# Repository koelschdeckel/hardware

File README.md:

Introduction
============

^^dkl is an Open Source hardware project that is being developed in
cooperation between the City of Cologne and Press Any Key UG. The
platform is intended to bridge the gap between devices similar to
Arduino, which allow physical access to sensors via electronic protocols
and device like Raspberry Pi that allow comfortable programming and
access to higher level facilities like Ethernet, USB and Bluetooth at
the cost of system complexity.

The system is intended to be used with applications that require
immediate interaction with the physical world, but need to interact with
the Internet or user devices. Furthermore, technical expertise required
to customise and operate the platform should be reduced to a minimum.

[Find out more](http://koelschdeckel.github.io/)

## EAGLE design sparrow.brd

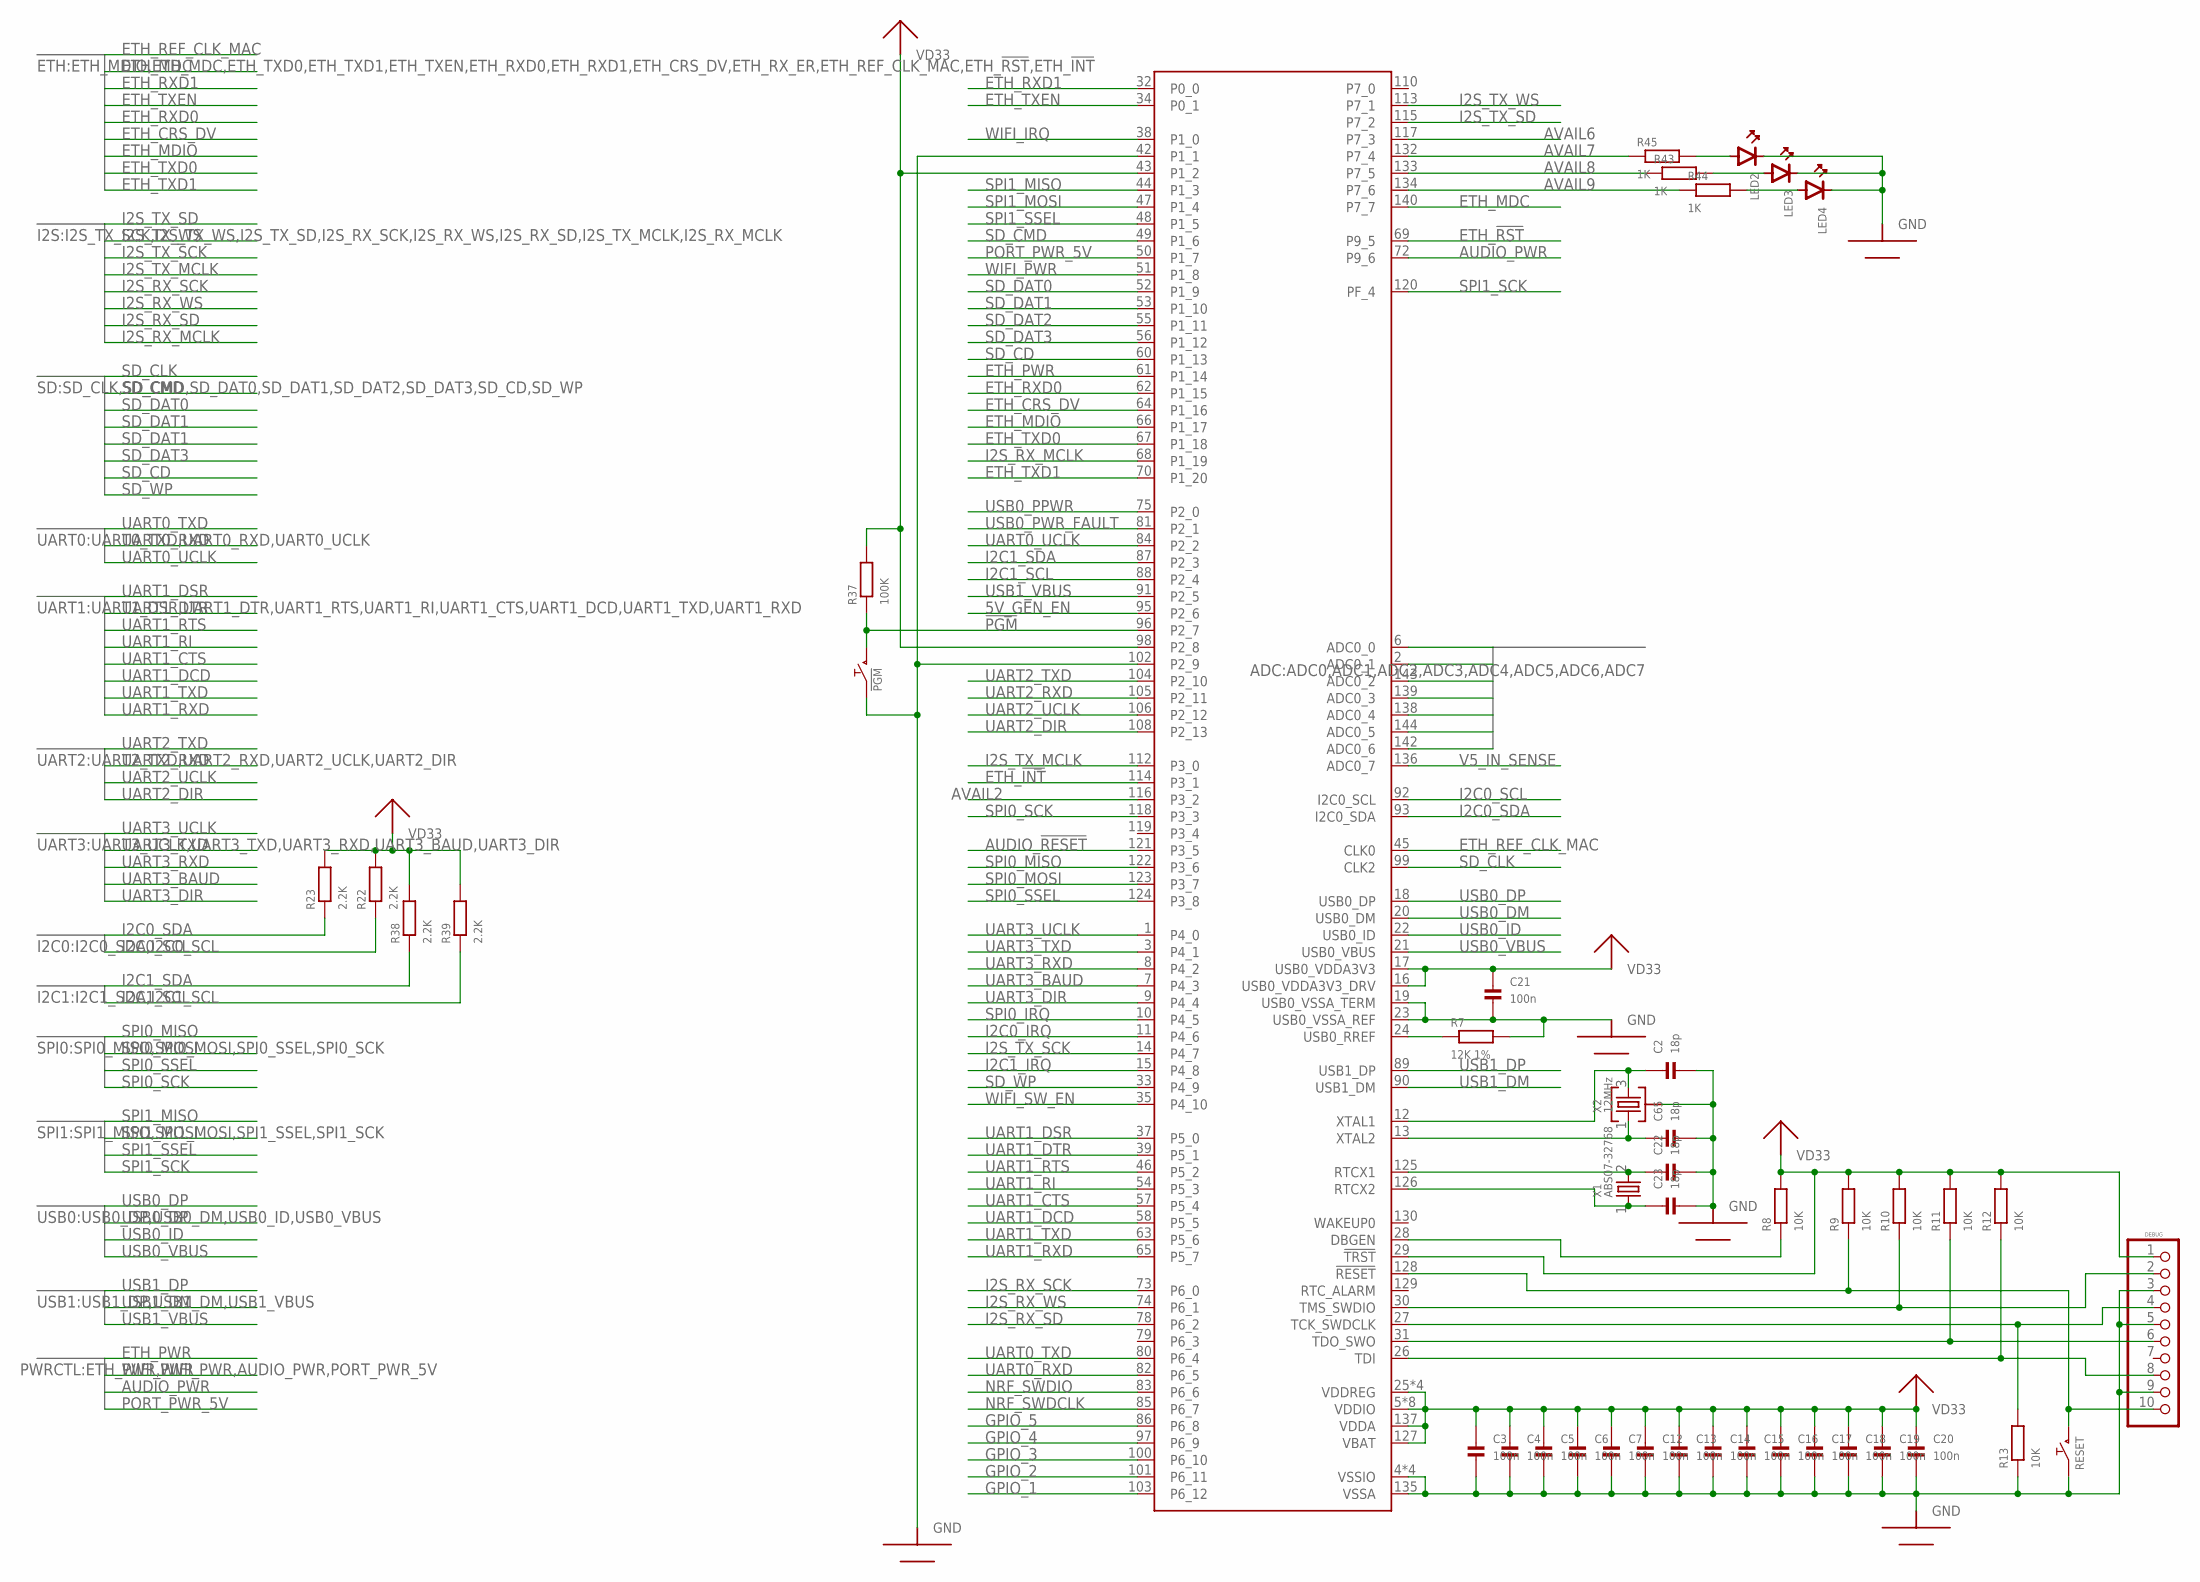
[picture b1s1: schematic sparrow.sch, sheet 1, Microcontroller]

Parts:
!PGM: PUSHBUTTONKMR2XX; CK-KMR2
C2, C22, C23, C65: 18p; 0603
C3, C4, C5, C6, C7, C12, C13, C14, C15, C16, C17, C18, C19, C20, C21: 100n; 0603
LED2, LED3, LED4: LED0603; 0603_POLAR
LPC_DEBUG: DEBUG; 2X05_SMT
MCU: LPC1837; QFP144-0.5
R7: 12K 1%; 0603
R8, R9, R10, R11, R12, R13: 10K; 0603
R22, R23, R38, R39: 2.2K; 0603
R37: 100K; 0603
R43, R44, R45: 1K; 0603
RESET: PUSHBUTTONKMR2XX; CK-KMR2
X1: ABS07-32768; 1206_MINIMELF_COMBO
X2: 12MHz; ABM8G

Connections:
5V_GEN_EN: MCU.95 (P2_6); also elsewhere on the board
!PGM: !PGM.P$3 (2), !PGM.P$4 (2), MCU.96 (P2_7), R37.1
!RESET: LPC_DEBUG.10, MCU.128 (!RESET), R9.1, RESET.P$3 (2), RESET.P$4 (2)
ADC0: MCU.6 (ADC0_0); also elsewhere on the board
ADC1: MCU.2 (ADC0_1); also elsewhere on the board
ADC2: MCU.143 (ADC0_2); also elsewhere on the board
ADC3: MCU.139 (ADC0_3); also elsewhere on the board
ADC4: MCU.138 (ADC0_4); also elsewhere on the board
ADC5: MCU.144 (ADC0_5); also elsewhere on the board
ADC6: MCU.142 (ADC0_6); also elsewhere on the board
AUDIO_!RESET: MCU.121 (P3_5); also elsewhere on the board
AUDIO_PWR: MCU.72 (P9_6); also elsewhere on the board
AVAIL2: MCU.116 (P3_2)
AVAIL6: MCU.117 (P7_3)
AVAIL7: MCU.132 (P7_4), R45.1
AVAIL8: MCU.133 (P7_5), R43.1
AVAIL9: MCU.134 (P7_6), R44.1
DBGEN: MCU.28 (DBGEN), R8.1
ETH_!INT: MCU.114 (P3_1); also elsewhere on the board
ETH_!RST: MCU.69 (P9_5); also elsewhere on the board
ETH_CRS_DV: MCU.64 (P1_16); also elsewhere on the board
ETH_MDC: MCU.140 (P7_7); also elsewhere on the board
ETH_MDIO: MCU.66 (P1_17); also elsewhere on the board
ETH_PWR: MCU.61 (P1_14); also elsewhere on the board
ETH_REF_CLK_MAC: MCU.45 (CLK0); also elsewhere on the board
ETH_RXD0: MCU.62 (P1_15); also elsewhere on the board
ETH_RXD1: MCU.32 (P0_0); also elsewhere on the board
ETH_TXD0: MCU.67 (P1_18); also elsewhere on the board
ETH_TXD1: MCU.70 (P1_20); also elsewhere on the board
ETH_TXEN: MCU.34 (P0_1); also elsewhere on the board
GND: !PGM.P$1 (1), !PGM.P$2 (1), C2.2, C3.2, C4.2, C5.2, C6.2, C7.2, C12.2, C13.2, C14.2, C15.2, C16.2, C17.2, C18.2, C19.2, C20.2, C21.2, C22.2, C23.2, C65.2, LED2.K (CATHODE), LED3.K (CATHODE), LED4.K (CATHODE), LPC_DEBUG.3, LPC_DEBUG.5, LPC_DEBUG.9, MCU.4 (VSSIO), MCU.19 (USB0_VSSA_TERM), MCU.23 (USB0_VSSA_REF), MCU.40 (VSSIO), MCU.42 (P1_1), MCU.76 (VSSIO), MCU.102 (P2_9), MCU.109 (VSSIO), MCU.135 (VSSA), R7.2, R13.1, RESET.P$1 (1), RESET.P$2 (1), X2.2 (GND), X2.4 (GND); also elsewhere on the board
GPIO_1: MCU.103 (P6_12); also elsewhere on the board
GPIO_2: MCU.101 (P6_11); also elsewhere on the board
GPIO_3: MCU.100 (P6_10); also elsewhere on the board
GPIO_4: MCU.97 (P6_9); also elsewhere on the board
GPIO_5: MCU.86 (P6_8); also elsewhere on the board
I2C0_IRQ: MCU.11 (P4_6); also elsewhere on the board
I2C0_SCL: MCU.92 (I2C0_SCL), R22.1; also elsewhere on the board
I2C0_SDA: MCU.93 (I2C0_SDA), R23.1; also elsewhere on the board
I2C1_IRQ: MCU.15 (P4_8); also elsewhere on the board
I2C1_SCL: MCU.88 (P2_4), R39.1; also elsewhere on the board
I2C1_SDA: MCU.87 (P2_3), R38.1; also elsewhere on the board
I2S_RX_MCLK: MCU.68 (P1_19); also elsewhere on the board
I2S_RX_SCK: MCU.73 (P6_0); also elsewhere on the board
I2S_RX_SD: MCU.78 (P6_2); also elsewhere on the board
I2S_RX_WS: MCU.74 (P6_1); also elsewhere on the board
I2S_TX_MCLK: MCU.112 (P3_0); also elsewhere on the board
I2S_TX_SCK: MCU.14 (P4_7); also elsewhere on the board
I2S_TX_SD: MCU.115 (P7_2); also elsewhere on the board
I2S_TX_WS: MCU.113 (P7_1); also elsewhere on the board
unnamed: LED2.A (ANODE), R45.2
unnamed: LED3.A (ANODE), R43.2
unnamed: LED4.A (ANODE), R44.2
NRF_SWDCLK: MCU.85 (P6_7); also elsewhere on the board
NRF_SWDIO: MCU.83 (P6_6); also elsewhere on the board
PORT_PWR_5V: MCU.50 (P1_7); also elsewhere on the board
RTXC1: C22.1, MCU.125 (RTCX1), X1.2
RTXC2: C23.1, MCU.126 (RTCX2), X1.1
SD_CD: MCU.60 (P1_13); also elsewhere on the board
SD_CLK: MCU.99 (CLK2); also elsewhere on the board
SD_CMD: MCU.49 (P1_6); also elsewhere on the board
SD_DAT0: MCU.52 (P1_9); also elsewhere on the board
SD_DAT1: MCU.53 (P1_10); also elsewhere on the board
SD_DAT2: MCU.55 (P1_11); also elsewhere on the board
SD_DAT3: MCU.56 (P1_12); also elsewhere on the board
SD_WP: MCU.33 (P4_9); also elsewhere on the board
SPI0_IRQ: MCU.10 (P4_5); also elsewhere on the board
SPI0_MISO: MCU.122 (P3_6); also elsewhere on the board
SPI0_MOSI: MCU.123 (P3_7); also elsewhere on the board
SPI0_SCK: MCU.118 (P3_3); also elsewhere on the board
SPI0_SSEL: MCU.124 (P3_8); also elsewhere on the board
SPI1_MISO: MCU.44 (P1_3); also elsewhere on the board
SPI1_MOSI: MCU.47 (P1_4); also elsewhere on the board
SPI1_SCK: MCU.120 (PF_4); also elsewhere on the board
SPI1_SSEL: MCU.48 (P1_5); also elsewhere on the board
SWDCLK: LPC_DEBUG.4, MCU.27 (TCK_SWDCLK), R13.2
SWDIO: LPC_DEBUG.2, MCU.30 (TMS_SWDIO), R10.1
TDI: LPC_DEBUG.8, MCU.26 (TDI), R12.1
TDO_SWO: LPC_DEBUG.6, MCU.31 (TDO_SWO), R11.1
UART0_RXD: MCU.82 (P6_5); also elsewhere on the board
UART0_TXD: MCU.80 (P6_4); also elsewhere on the board
UART0_UCLK: MCU.84 (P2_2); also elsewhere on the board
UART1_CTS: MCU.57 (P5_4); also elsewhere on the board
UART1_DCD: MCU.58 (P5_5)
UART1_DSR: MCU.37 (P5_0)
UART1_DTR: MCU.39 (P5_1)
UART1_RI: MCU.54 (P5_3)
UART1_RTS: MCU.46 (P5_2); also elsewhere on the board
UART1_RXD: MCU.65 (P5_7); also elsewhere on the board
UART1_TXD: MCU.63 (P5_6); also elsewhere on the board
UART2_DIR: MCU.108 (P2_13); also elsewhere on the board
UART2_RXD: MCU.105 (P2_11); also elsewhere on the board
UART2_TXD: MCU.104 (P2_10); also elsewhere on the board
UART2_UCLK: MCU.106 (P2_12); also elsewhere on the board
UART3_BAUD: MCU.7 (P4_3); also elsewhere on the board
UART3_DIR: MCU.9 (P4_4); also elsewhere on the board
UART3_RXD: MCU.8 (P4_2); also elsewhere on the board
UART3_TXD: MCU.3 (P4_1); also elsewhere on the board
UART3_UCLK: MCU.1 (P4_0); also elsewhere on the board
USB0_DM: MCU.20 (USB0_DM); also elsewhere on the board
USB0_DP: MCU.18 (USB0_DP); also elsewhere on the board
USB0_ID: MCU.22 (USB0_ID); also elsewhere on the board
USB0_PPWR: MCU.75 (P2_0); also elsewhere on the board
USB0_PWR_FAULT: MCU.81 (P2_1); also elsewhere on the board
USB0_RREF: MCU.24 (USB0_RREF), R7.1
USB0_VBUS: MCU.21 (USB0_VBUS); also elsewhere on the board
USB1_DM: MCU.90 (USB1_DM); also elsewhere on the board
USB1_DP: MCU.89 (USB1_DP); also elsewhere on the board
USB1_VBUS: MCU.91 (P2_5); also elsewhere on the board
V5_IN_SENSE: MCU.136 (ADC0_7); also elsewhere on the board
VD33: C3.1, C4.1, C5.1, C6.1, C7.1, C12.1, C13.1, C14.1, C15.1, C16.1, C17.1, C18.1, C19.1, C20.1, C21.1, LPC_DEBUG.1, MCU.5 (VDDIO), MCU.16 (USB0_VDDA3V3_DRV), MCU.17 (USB0_VDDA3V3), MCU.25 (VDDREG), MCU.29 (!TRST), MCU.36 (VDDIO), MCU.41 (VDDIO), MCU.43 (P1_2), MCU.59 (VDDREG), MCU.71 (VDDIO), MCU.77 (VDDIO), MCU.94 (VDDREG), MCU.98 (P2_8), MCU.107 (VDDIO), MCU.111 (VDDIO), MCU.127 (VBAT), MCU.131 (VDDREG), MCU.137 (VDDA), MCU.141 (VDDIO), R8.2, R9.2, R10.2, R11.2, R12.2, R22.2, R23.2, R37.2, R38.2, R39.2; also elsewhere on the board
WIFI_IRQ: MCU.38 (P1_0); also elsewhere on the board
WIFI_PWR: MCU.51 (P1_8); also elsewhere on the board
WIFI_SW_EN: MCU.35 (P4_10); also elsewhere on the board
XTAL1: C2.1, MCU.12 (XTAL1), X2.3 (2)
XTAL2: C65.1, MCU.13 (XTAL2), X2.1

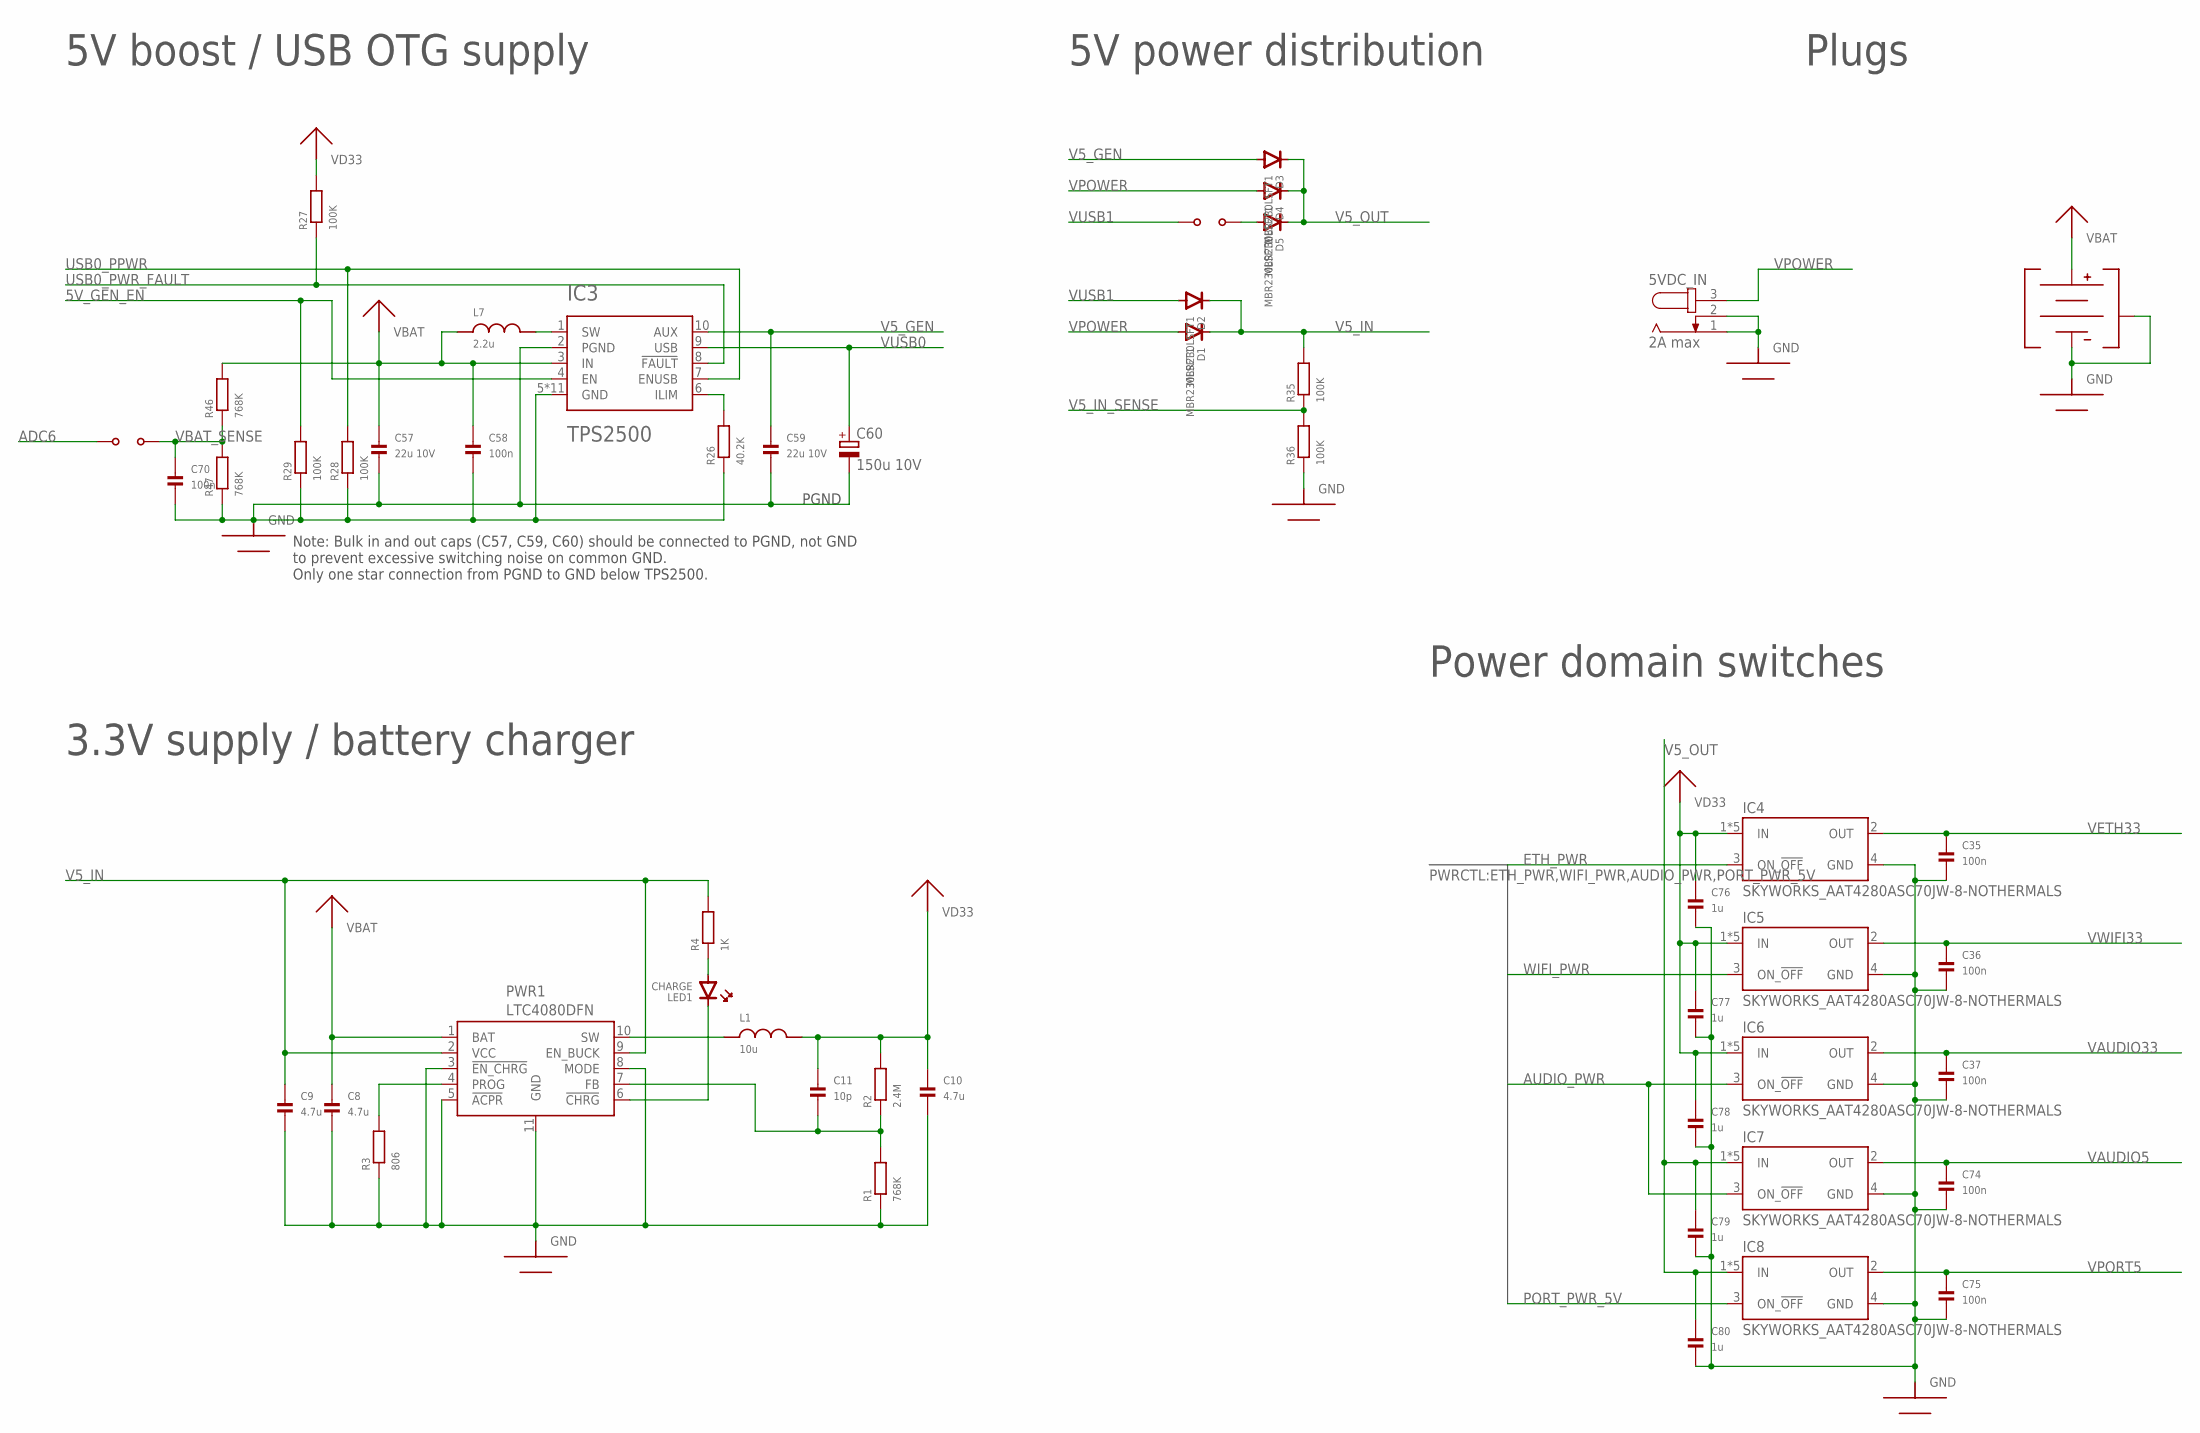
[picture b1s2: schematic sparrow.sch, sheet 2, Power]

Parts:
5VDC_IN: 2A max; CUI_PJ_102BH
BATSNS: JUMPERSOLDER_CLOSED; 0603_SOLDERJUMPER_CLOSED
BATT: BATTERY_WITH_HOLDER; S2B-PH-SM4-TB
C8, C9, C10: 4.7u; 0603
C11: 10p; 0603
C35, C36, C37, C58, C70, C74, C75: 100n; 0603
C57, C59: 22u 10V; 0805
C60: 150u 10V; 1210_POLAR
C76, C77, C78, C79, C80: 1u; 0603
D1, D2, D3, D4, D5: MBR230LSFT1; SOD123FL
IC3: TPS2500; SON10-0.5-EP-VIAS
IC4, IC5, IC6, IC7, IC8: SKYWORKS_AAT4280ASC70JW-8-NOTHERMALS; SC70JW-8-NOTHERMALS
L1: 10u; INDUCTOR_40X40
L7: 2.2u; INDUCTOR_40X40
LED1: CHARGE; 0603_POLAR
LIM: JUMPERSOLDER_OPEN; 0603_SOLDERJUMPER_OPEN
PWR1: LTC4080DFN; LTC4080_DFN
R1, R46, R47: 768K; 0603
R2: 2.4M; 0603
R3: 806; 0603
R4: 1K; 0603
R26: 40.2K; 0603
R27, R28, R29, R35, R36: 100K; 0603

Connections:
5V_BOOST_SW: IC3.1 (SW), L7.P$2 (2)
5V_GEN_EN: IC3.4 (EN), R29.2; also elsewhere on the board
5V_ILIM: IC3.6 (ILIM), R26.2
ADC6: BATSNS.1; also elsewhere on the board
AUDIO_PWR: IC6.3 (ON_!OFF), IC7.3 (ON_!OFF); also elsewhere on the board
CHARGE_!CHRG: LED1.K (CATHODE), PWR1.6 (!CHRG)
CHARGE_!CHRG_CURR: LED1.A (ANODE), R4.1
CHARGE_FB: C11.2, PWR1.7 (FB), R1.2, R2.1
CHARGE_PROG: PWR1.4 (PROG), R3.2
CHARGE_SW: L1.P$1 (1), PWR1.10 (SW)
ETH_PWR: IC4.3 (ON_!OFF); also elsewhere on the board
GND: 5VDC_IN.1, 5VDC_IN.2, BATT.2 (-), BATT.3 (HOLDER), BATT.4 (HOLDER), C8.2, C9.2, C10.2, C35.2, C36.2, C37.2, C57.2, C58.2, C59.2, C60.K (-), C70.2, C74.2, C75.2, C76.2, C77.2, C78.2, C79.2, C80.2, IC3.2 (PGND), IC3.5 (GND), IC3.EXT1 (GND), IC3.EXT2 (GND), IC3.EXT3 (GND), IC3.EXT4 (GND), IC3.PAD (GND), IC3.THERM1 (GND), IC3.THERM2 (GND), IC3.THERM3 (GND), IC3.THERM4 (GND), IC3.THERM5 (GND), IC4.4 (GND), IC5.4 (GND), IC6.4 (GND), IC7.4 (GND), IC8.4 (GND), PWR1.3 (!EN_CHRG), PWR1.5 (!ACPR), PWR1.8 (MODE), PWR1.11 (GND), R1.1, R3.1, R26.1, R28.1, R29.1, R36.1, R47.1; also elsewhere on the board
PORT_PWR_5V: IC8.3 (ON_!OFF); also elsewhere on the board
USB0_PPWR: IC3.7 (ENUSB), R28.2; also elsewhere on the board
USB0_PWR_FAULT: IC3.8 (!FAULT), R27.1; also elsewhere on the board
V5_GEN: C59.1, D3.A (ANODE), IC3.10 (AUX)
V5_IN: C9.1, D1.K (CATHODE), D2.K (CATHODE), PWR1.2 (VCC), PWR1.9 (EN_BUCK), R4.2, R35.2
V5_IN_SENSE: R35.1, R36.2; also elsewhere on the board
V5_OUT: C79.1, C80.1, D3.K (CATHODE), D4.K (CATHODE), D5.K (CATHODE), IC7.1 (IN), IC7.5 (IN), IC7.6 (IN), IC7.7 (IN), IC7.8 (IN), IC8.1 (IN), IC8.5 (IN), IC8.6 (IN), IC8.7 (IN), IC8.8 (IN)
VAUDIO5: C74.1, IC7.2 (OUT); also elsewhere on the board
VAUDIO33: C37.1, IC6.2 (OUT); also elsewhere on the board
VBAT: BATT.1 (+), C8.1, C57.1, C58.1, IC3.3 (IN), L7.P$1 (1), PWR1.1 (BAT), R46.2
VBAT_SENSE: BATSNS.2, C70.1, R46.1, R47.2
VD33: C10.1, C11.1, C76.1, C77.1, C78.1, IC4.1 (IN), IC4.5 (IN), IC4.6 (IN), IC4.7 (IN), IC4.8 (IN), IC5.1 (IN), IC5.5 (IN), IC5.6 (IN), IC5.7 (IN), IC5.8 (IN), IC6.1 (IN), IC6.5 (IN), IC6.6 (IN), IC6.7 (IN), IC6.8 (IN), L1.P$2 (2), R2.2, R27.2; also elsewhere on the board
VETH33: C35.1, IC4.2 (OUT); also elsewhere on the board
VPORT5: C75.1, IC8.2 (OUT); also elsewhere on the board
VPOWER: 5VDC_IN.3, D1.A (ANODE), D4.A (ANODE)
VUSB0: C60.A (+), IC3.9 (USB); also elsewhere on the board
VUSB1: D2.A (ANODE), LIM.1; also elsewhere on the board
VUSB1_V5_OUT: D5.A (ANODE), LIM.2
VWIFI33: C36.1, IC5.2 (OUT); also elsewhere on the board
WIFI_PWR: IC5.3 (ON_!OFF); also elsewhere on the board

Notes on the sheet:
5V power distribution
5V boost / USB OTG supply
3.3V supply / battery charger
Power domain switches
Plugs
Note: Bulk in and out caps (C57, C59, C60) should be connected to PGND, not GND to prevent excessive switching noise on common GND. Only one star connection from PGND to GND below TPS2500.
PGND

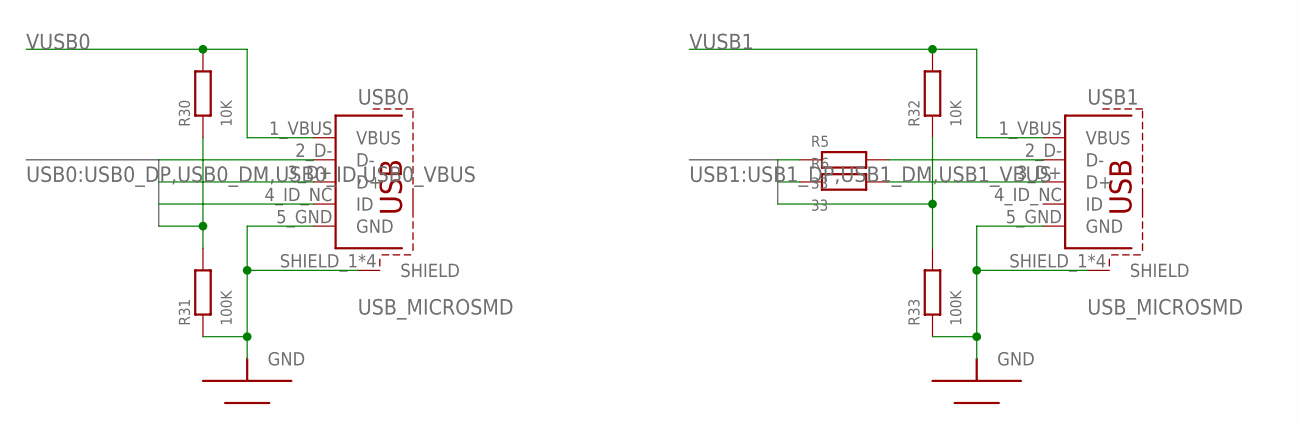
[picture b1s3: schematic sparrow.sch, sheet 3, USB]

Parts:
R5, R6: 33; 0603
R30, R32: 10K; 0603
R31, R33: 100K; 0603
USB0, USB1: USB_MICROSMD; USB_MICRO_SMD

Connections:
GND: R31.1, R33.1, USB0.5_GND (GND), USB0.SHIELD_1 (SHIELD), USB0.SHIELD_2 (SHIELD), USB0.SHIELD_3 (SHIELD), USB0.SHIELD_4 (SHIELD), USB1.5_GND (GND), USB1.SHIELD_1 (SHIELD), USB1.SHIELD_2 (SHIELD), USB1.SHIELD_3 (SHIELD), USB1.SHIELD_4 (SHIELD); also elsewhere on the board
USB0_DM: USB0.2_D- (D-); also elsewhere on the board
USB0_DP: USB0.3_D+ (D+); also elsewhere on the board
USB0_ID: USB0.4_ID_NC (ID); also elsewhere on the board
USB0_VBUS: R30.1, R31.2; also elsewhere on the board
USB1_DM: R5.1; also elsewhere on the board
USB1_DM_LINE: R5.2, USB1.2_D- (D-)
USB1_DP: R6.1; also elsewhere on the board
USB1_VBUS: R32.1, R33.2; also elsewhere on the board
USB_DP_LINE: R6.2, USB1.3_D+ (D+)
VUSB0: R30.2, USB0.1_VBUS (VBUS); also elsewhere on the board
VUSB1: R32.2, USB1.1_VBUS (VBUS); also elsewhere on the board

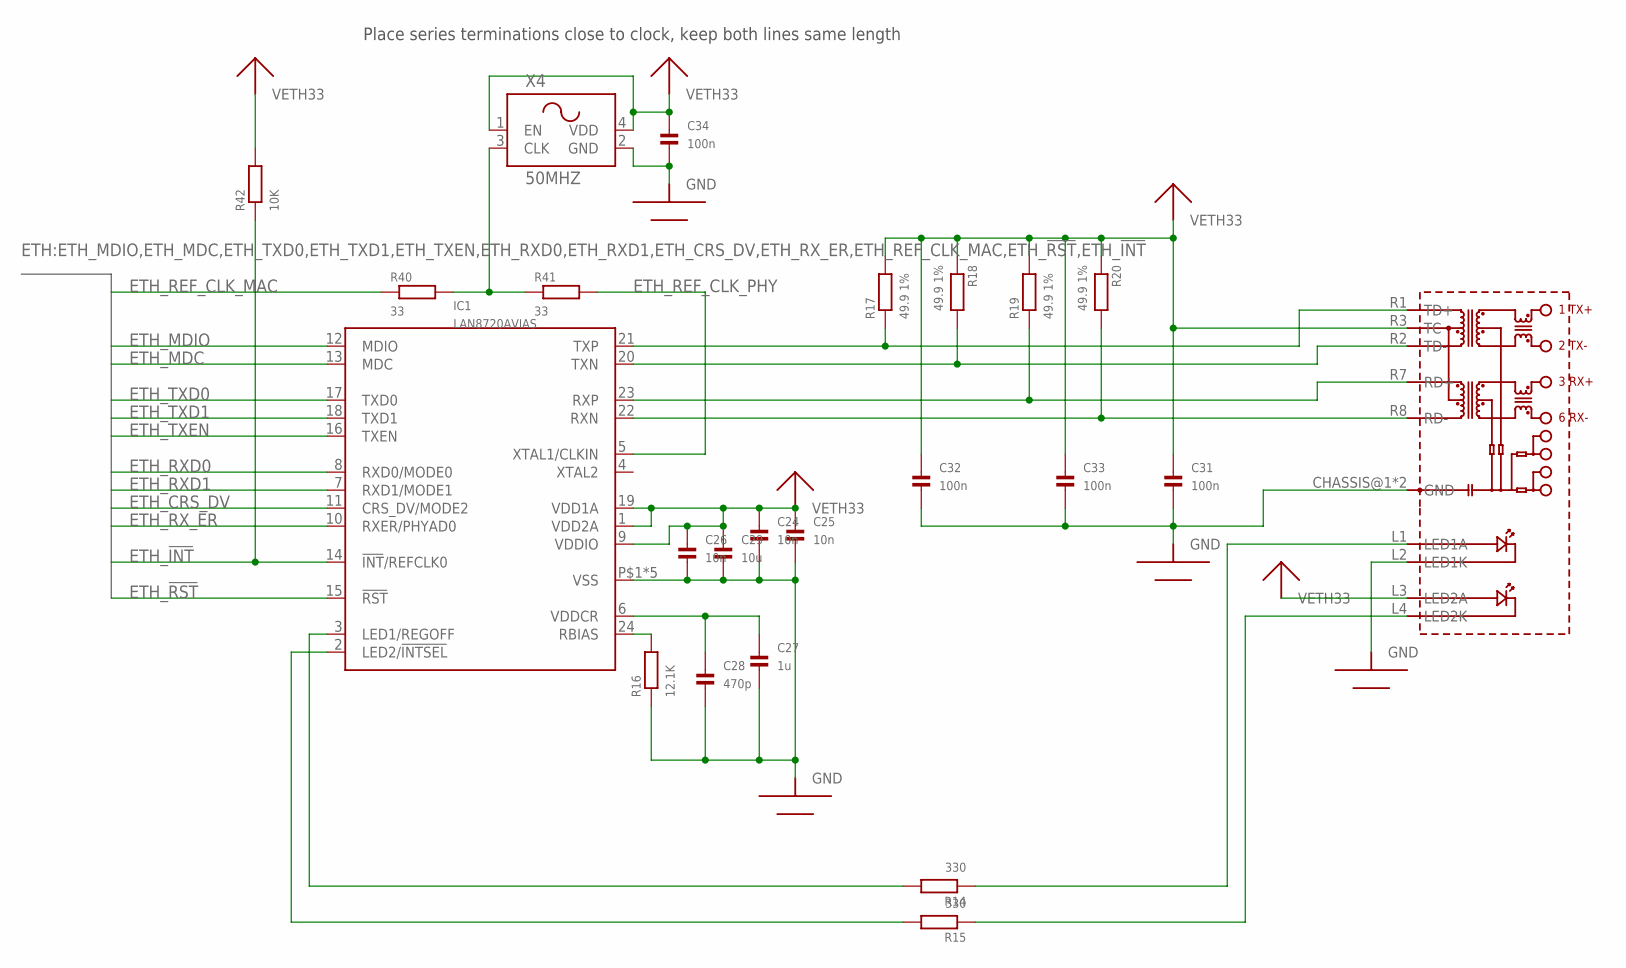
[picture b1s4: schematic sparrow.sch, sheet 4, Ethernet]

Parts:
C24, C25, C26: 10n; 0603
C27: 1u; 0603
C28: 470p; 0603
C29: 10u; 0603
C31, C32, C33, C34: 100n; 0603
ETH: ETHERNET_JACK_LEDSRB1-125BAG1A; RJ45-RB1-125BAG1A
IC1: LAN8720AVIAS; QFN24-0.5-EP-VIAS
R14, R15: 330; 0603
R16: 12.1K; 0603
R17, R18, R19, R20: 49.9 1%; 0603
R40, R41: 33; 0603
R42: 10K; 0603
X4: 50MHZ; CRYSTAL25X20

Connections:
ETH_!INT: IC1.14 (!INT!/REFCLK0), R42.1; also elsewhere on the board
ETH_!RST: IC1.15 (!RST); also elsewhere on the board
ETH_CRS_DV: IC1.11 (CRS_DV/MODE2); also elsewhere on the board
ETH_LED1: IC1.3 (LED1/REGOFF), R14.2
ETH_LED1_CURR: ETH.L1 (LED1A), R14.1
ETH_LED2: IC1.2 (LED2/!INTSEL), R15.2
ETH_LED2_CURR: ETH.L4 (LED2K), R15.1
ETH_MDC: IC1.13 (MDC); also elsewhere on the board
ETH_MDIO: IC1.12 (MDIO); also elsewhere on the board
ETH_RBIAS: IC1.24 (RBIAS), R16.2
ETH_REF_CLK: R40.2, R41.1, X4.3 (CLK)
ETH_REF_CLK_MAC: R40.1; also elsewhere on the board
ETH_REF_CLK_PHY: IC1.5 (XTAL1/CLKIN), R41.2
ETH_RXD0: IC1.8 (RXD0/MODE0); also elsewhere on the board
ETH_RXD1: IC1.7 (RXD1/MODE1); also elsewhere on the board
ETH_RXN: ETH.R8 (RD-), IC1.22 (RXN), R20.2
ETH_RXP: ETH.R7 (RD+), IC1.23 (RXP), R19.1
ETH_RX_ER: IC1.10 (RXER/PHYAD0)
ETH_TXD0: IC1.17 (TXD0); also elsewhere on the board
ETH_TXD1: IC1.18 (TXD1); also elsewhere on the board
ETH_TXEN: IC1.16 (TXEN); also elsewhere on the board
ETH_TXN: ETH.R2 (TD-), IC1.20 (TXN), R18.2
ETH_TXP: ETH.R1 (TD+), IC1.21 (TXP), R17.1
ETH_VDDCR: C27.1, C28.1, IC1.6 (VDDCR)
GND: C24.2, C25.2, C26.2, C27.2, C28.2, C29.2, C31.2, C32.2, C33.2, C34.2, ETH.CHASSIS@1 (GND), ETH.CHASSIS@2 (GND), ETH.L2 (LED1K), IC1.P$1 (VSS), IC1.P$2 (VSS), IC1.P$3 (VSS), IC1.P$4 (VSS), IC1.PAD (VSS), R16.1, X4.2 (GND); also elsewhere on the board
VETH33: C24.1, C25.1, C26.1, C29.1, C31.1, C32.1, C33.1, C34.1, ETH.L3 (LED2A), ETH.R3 (TC), IC1.1 (VDD2A), IC1.9 (VDDIO), IC1.19 (VDD1A), R17.2, R18.1, R19.2, R20.1, R42.2, X4.1 (EN), X4.4 (VDD); also elsewhere on the board

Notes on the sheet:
Place series terminations close to clock, keep both lines same length

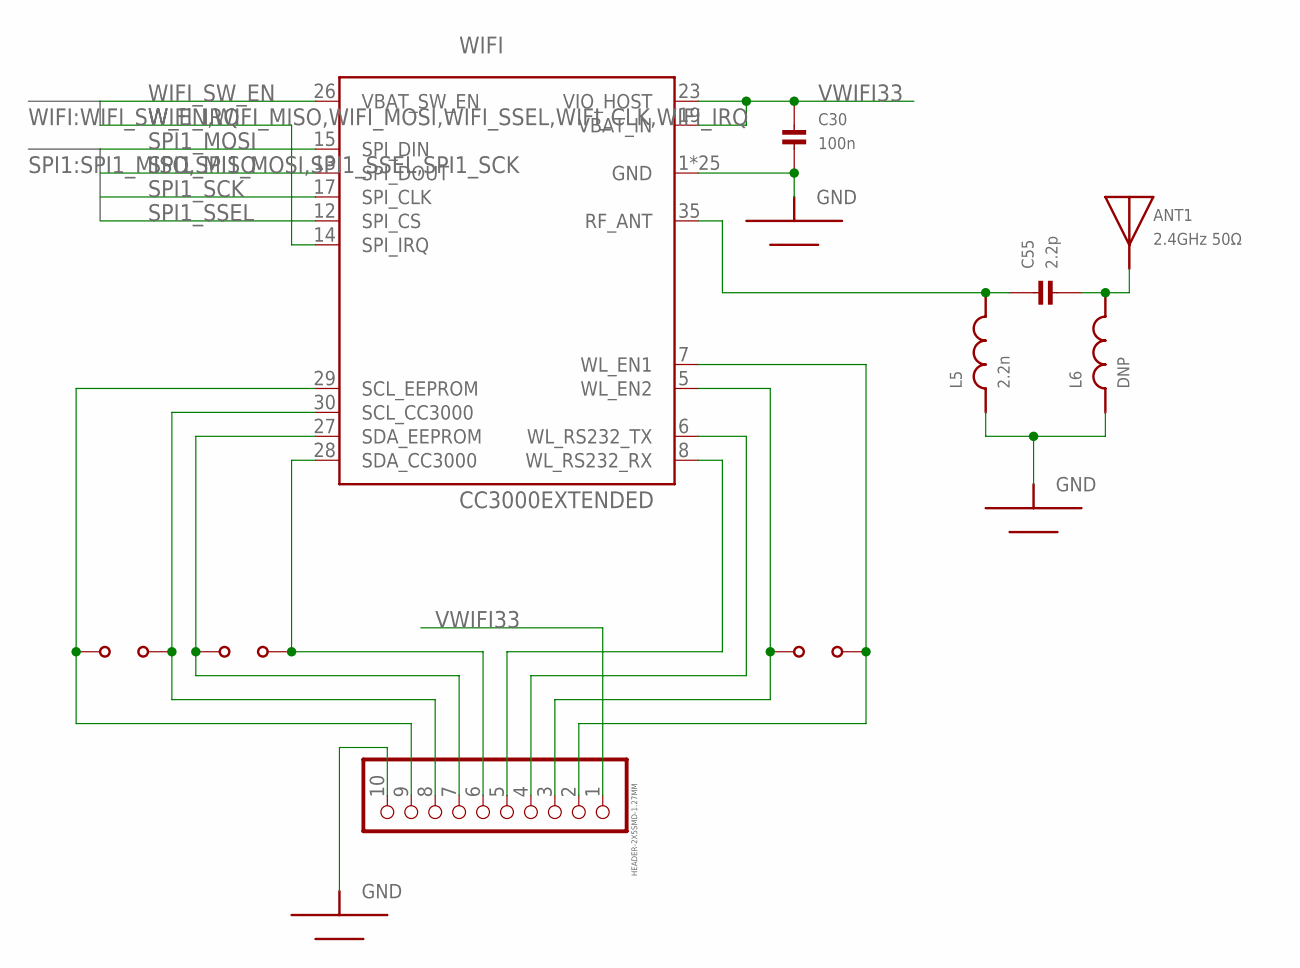
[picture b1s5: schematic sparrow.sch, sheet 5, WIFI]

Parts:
ANT1: 2.4GHz 50Ω; 1206_MINIMELF_COMBO
C30: 100n; 0603
C55: 2.2p; 0402
CC_DEBUG: HEADER-2X5SMD-1.27MM; 2X05_SMT
L5: 2.2n; 0402
L6: DNP; 0402
SCL: JUMPERSOLDER_CLOSED; 0603_SOLDERJUMPER_CLOSED
SDA: JUMPERSOLDER_CLOSED; 0603_SOLDERJUMPER_CLOSED
WIFI: CC3000EXTENDED; CC3000-EXT
WL_EN: JUMPERSOLDER_CLOSED; 0603_SOLDERJUMPER_CLOSED

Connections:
GND: C30.2, CC_DEBUG.10, L5.P$1 (1), L6.P$1 (1), WIFI.1 (GND), WIFI.9 (GND), WIFI.10 (GND), WIFI.11 (GND), WIFI.16 (GND), WIFI.18 (GND), WIFI.20 (GND), WIFI.21 (GND), WIFI.22 (GND), WIFI.25 (GND), WIFI.31 (GND), WIFI.32 (GND), WIFI.33 (GND), WIFI.34 (GND), WIFI.36 (GND), WIFI.37 (GND), WIFI.38 (GND), WIFI.39 (GND), WIFI.40 (GND), WIFI.41 (GND), WIFI.42 (GND), WIFI.43 (GND), WIFI.44 (GND), WIFI.45 (GND), WIFI.46 (GND); also elsewhere on the board
SPI1_MISO: WIFI.13 (SPI_DOUT); also elsewhere on the board
SPI1_MOSI: WIFI.15 (SPI_DIN); also elsewhere on the board
SPI1_SCK: WIFI.17 (SPI_CLK); also elsewhere on the board
SPI1_SSEL: WIFI.12 (SPI_CS); also elsewhere on the board
VWIFI33: C30.1, CC_DEBUG.1, WIFI.19 (VBAT_IN), WIFI.23 (VIO_HOST); also elsewhere on the board
WIFI_ANT: ANT1.1, C55.P$2, L6.P$2 (2)
WIFI_ANT_UNBAL: C55.P$1, L5.P$2 (2), WIFI.35 (RF_ANT)
WIFI_IRQ: WIFI.14 (SPI_IRQ); also elsewhere on the board
WIFI_SCL_CC3000: CC_DEBUG.8, SCL.1, WIFI.30 (SCL_CC3000)
WIFI_SCL_EEPROM: CC_DEBUG.9, SCL.2, WIFI.29 (SCL_EEPROM)
WIFI_SDA_CC3000: CC_DEBUG.6, SDA.1, WIFI.28 (SDA_CC3000)
WIFI_SDA_EEPROM: CC_DEBUG.7, SDA.2, WIFI.27 (SDA_EEPROM)
WIFI_SW_EN: WIFI.26 (VBAT_SW_EN); also elsewhere on the board
WL_EN1: CC_DEBUG.2, WIFI.7 (WL_EN1), WL_EN.1
WL_EN2: CC_DEBUG.3, WIFI.5 (WL_EN2), WL_EN.2
WL_RS232_RX: CC_DEBUG.5, WIFI.8 (WL_RS232_RX)
WL_RS232_TX: CC_DEBUG.4, WIFI.6 (WL_RS232_TX)

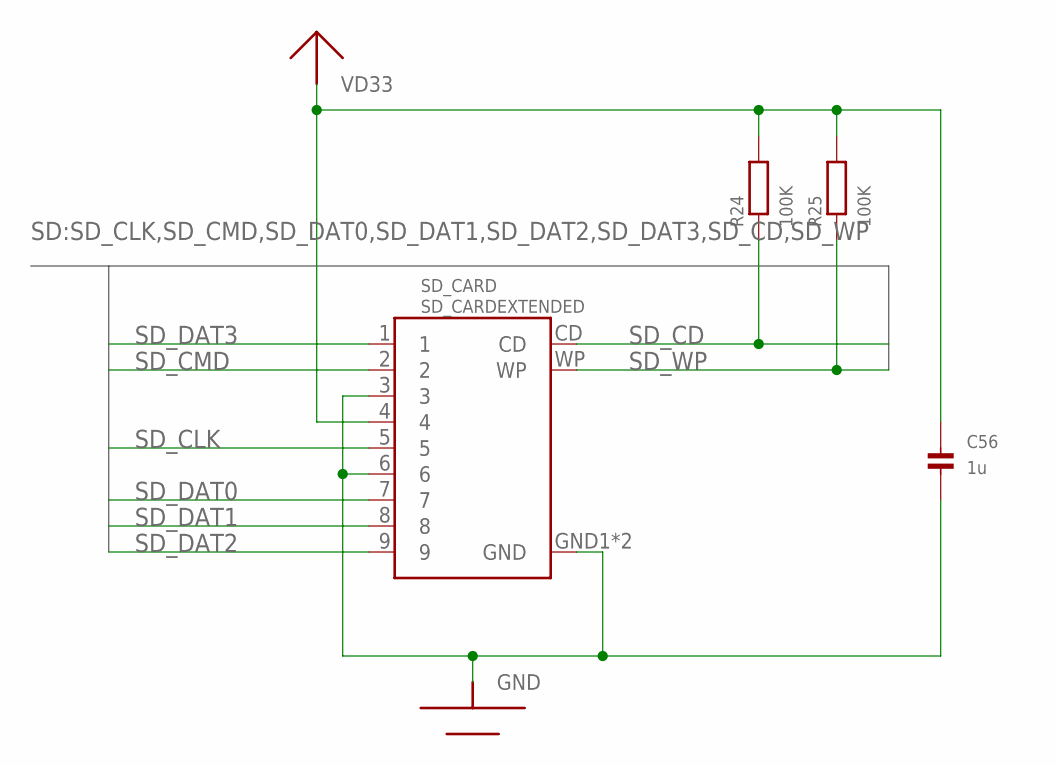
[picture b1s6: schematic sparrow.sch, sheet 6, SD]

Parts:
C56: 1u; 0603
R24, R25: 100K; 0603
SD_CARD: SD_CARDEXTENDED; AMPHENO_101_00313_EXT_PADS

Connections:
GND: C56.2, SD_CARD.3, SD_CARD.6, SD_CARD.GND1 (GND), SD_CARD.GND2 (GND); also elsewhere on the board
SD_CD: R24.1, SD_CARD.CD; also elsewhere on the board
SD_CLK: SD_CARD.5; also elsewhere on the board
SD_CMD: SD_CARD.2; also elsewhere on the board
SD_DAT0: SD_CARD.7; also elsewhere on the board
SD_DAT1: SD_CARD.8; also elsewhere on the board
SD_DAT2: SD_CARD.9; also elsewhere on the board
SD_DAT3: SD_CARD.1; also elsewhere on the board
SD_WP: R25.1, SD_CARD.WP; also elsewhere on the board
VD33: C56.1, R24.2, R25.2, SD_CARD.4; also elsewhere on the board
